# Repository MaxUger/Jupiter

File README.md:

# Jupiter
A 75% hotswappable keyboard PCB with adressable RGB backlighting

__THIS PCB IS UNTESTED, IT PROBABLY DOES NOT WORK__

## Features
- 75% Layout
- Hot-swappable
- Adressable RGB backlighting
- USB-C connectivity
- QMK compatible

## Microcontroller

- Atmel ATmega32u4-MU due to its compatibility with QMK.
- 16MHz crystal oscillator

## USB-C Assembly

- Uses TYPE-C-31-M-14 connector
- PRTR5V0U2X for ESD protection
- 500mA fuse for overcurrent protection

## Switch Matrix

- Features a traditional matrix

## LED Matrices

- Features SK6812MINI-E LEDs

__REMINDER: THIS PCB IS UNTESTED, IT PROBABLY DOES NOT WORK. THIS PROJECT IS PURELY A TECHNICAL EXERCISE__

__This project falls under the GNU General Public License v3.0. This project is provided without liability, warranty, and garentee of functionality.__

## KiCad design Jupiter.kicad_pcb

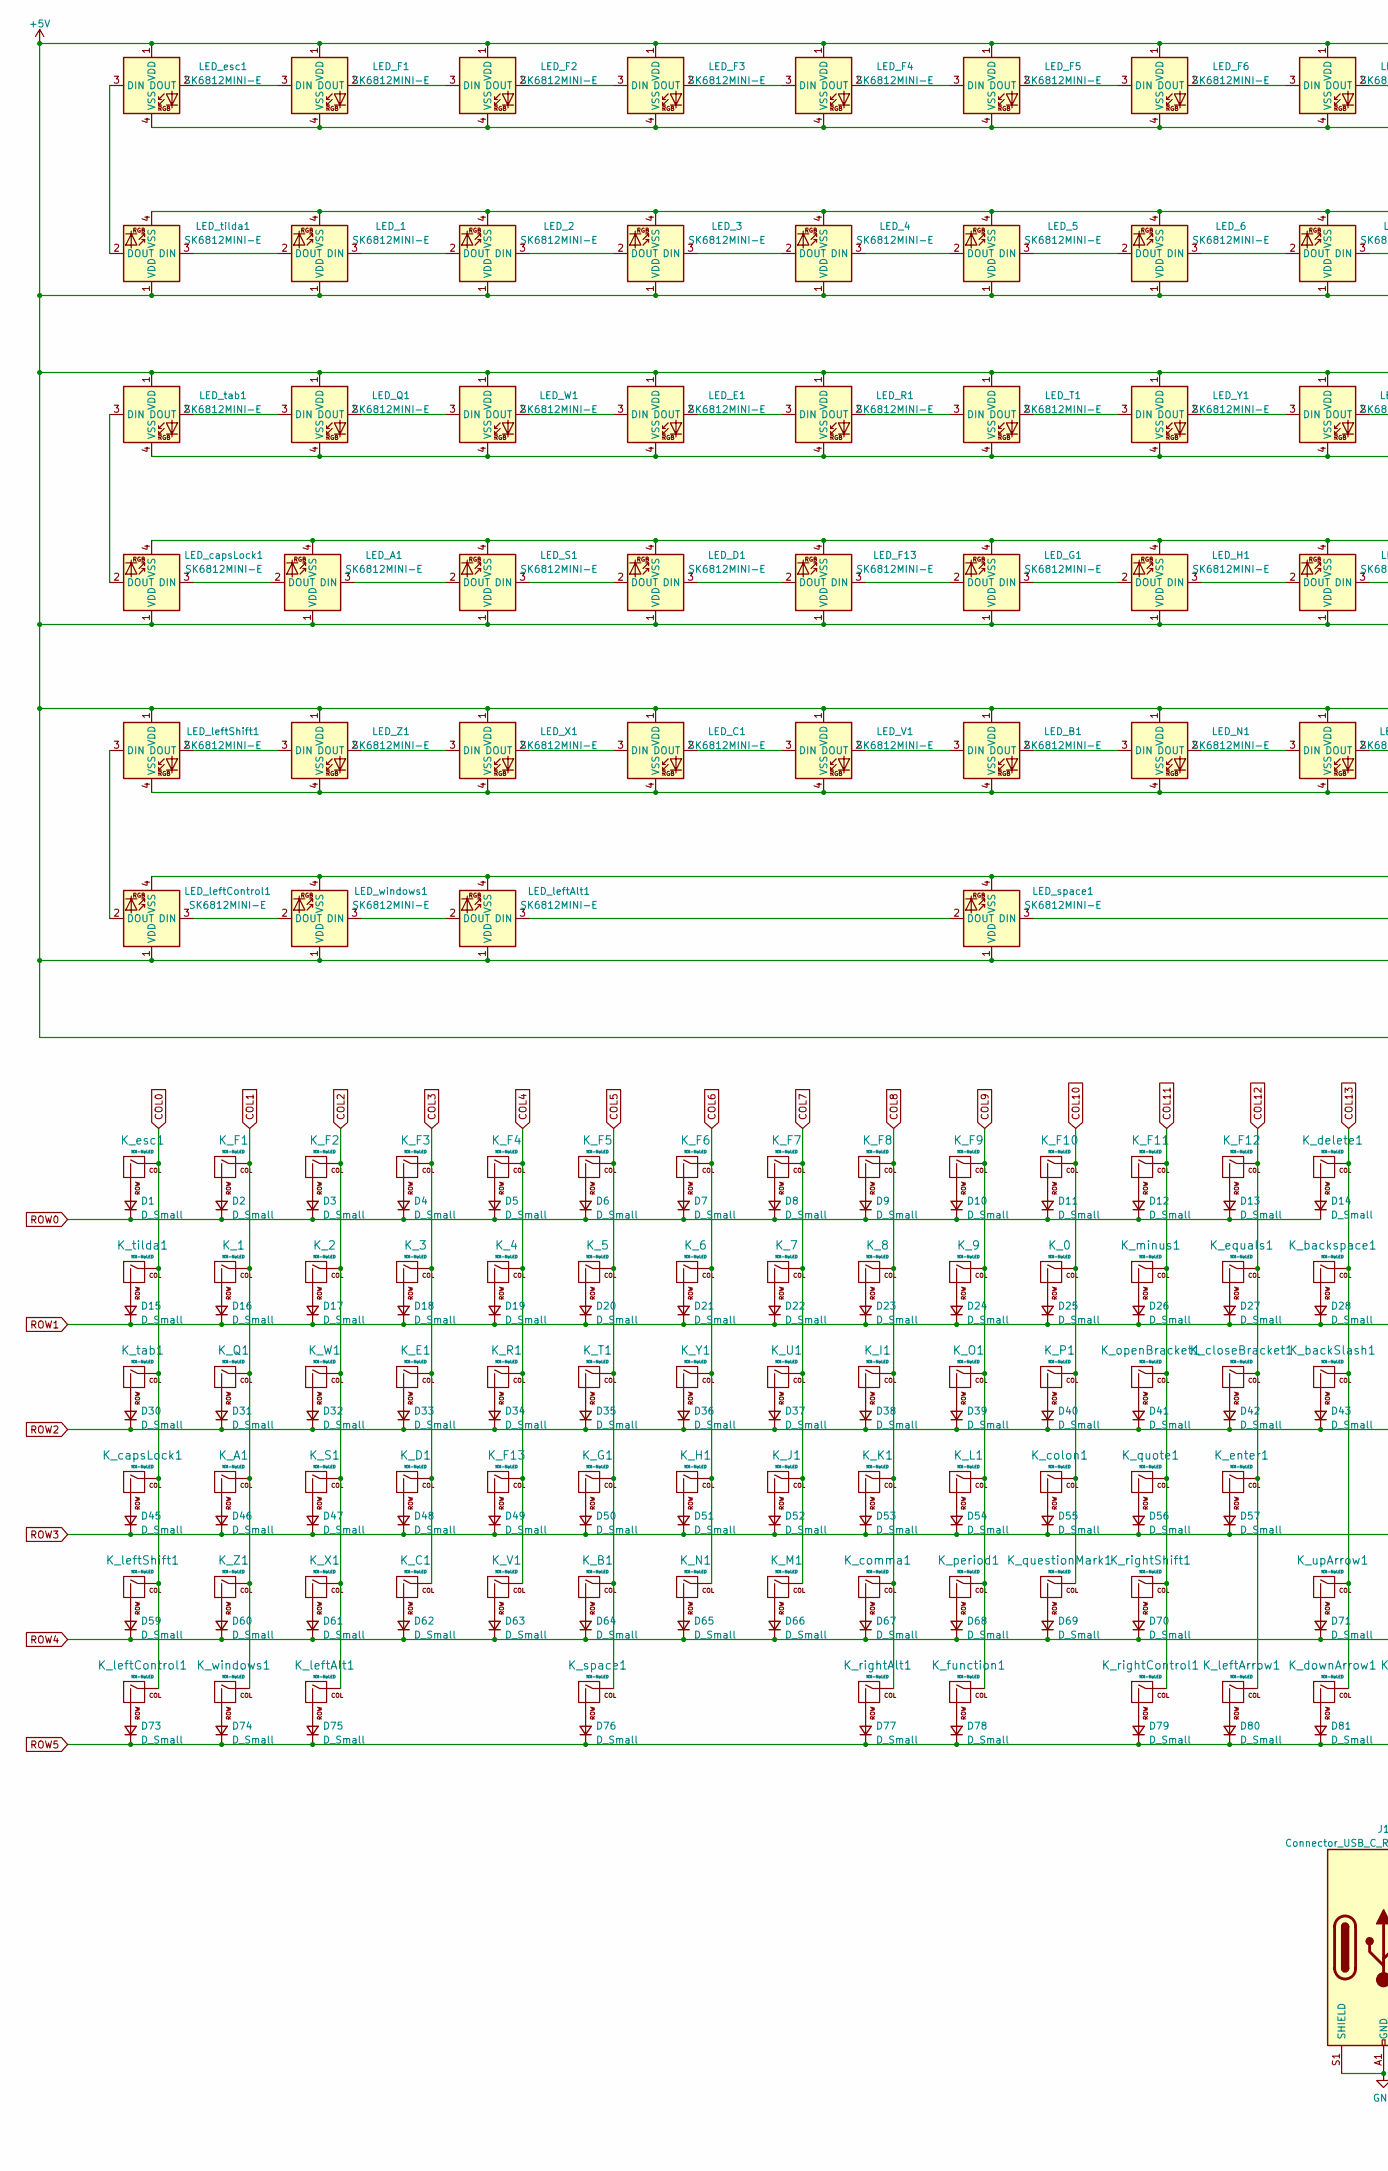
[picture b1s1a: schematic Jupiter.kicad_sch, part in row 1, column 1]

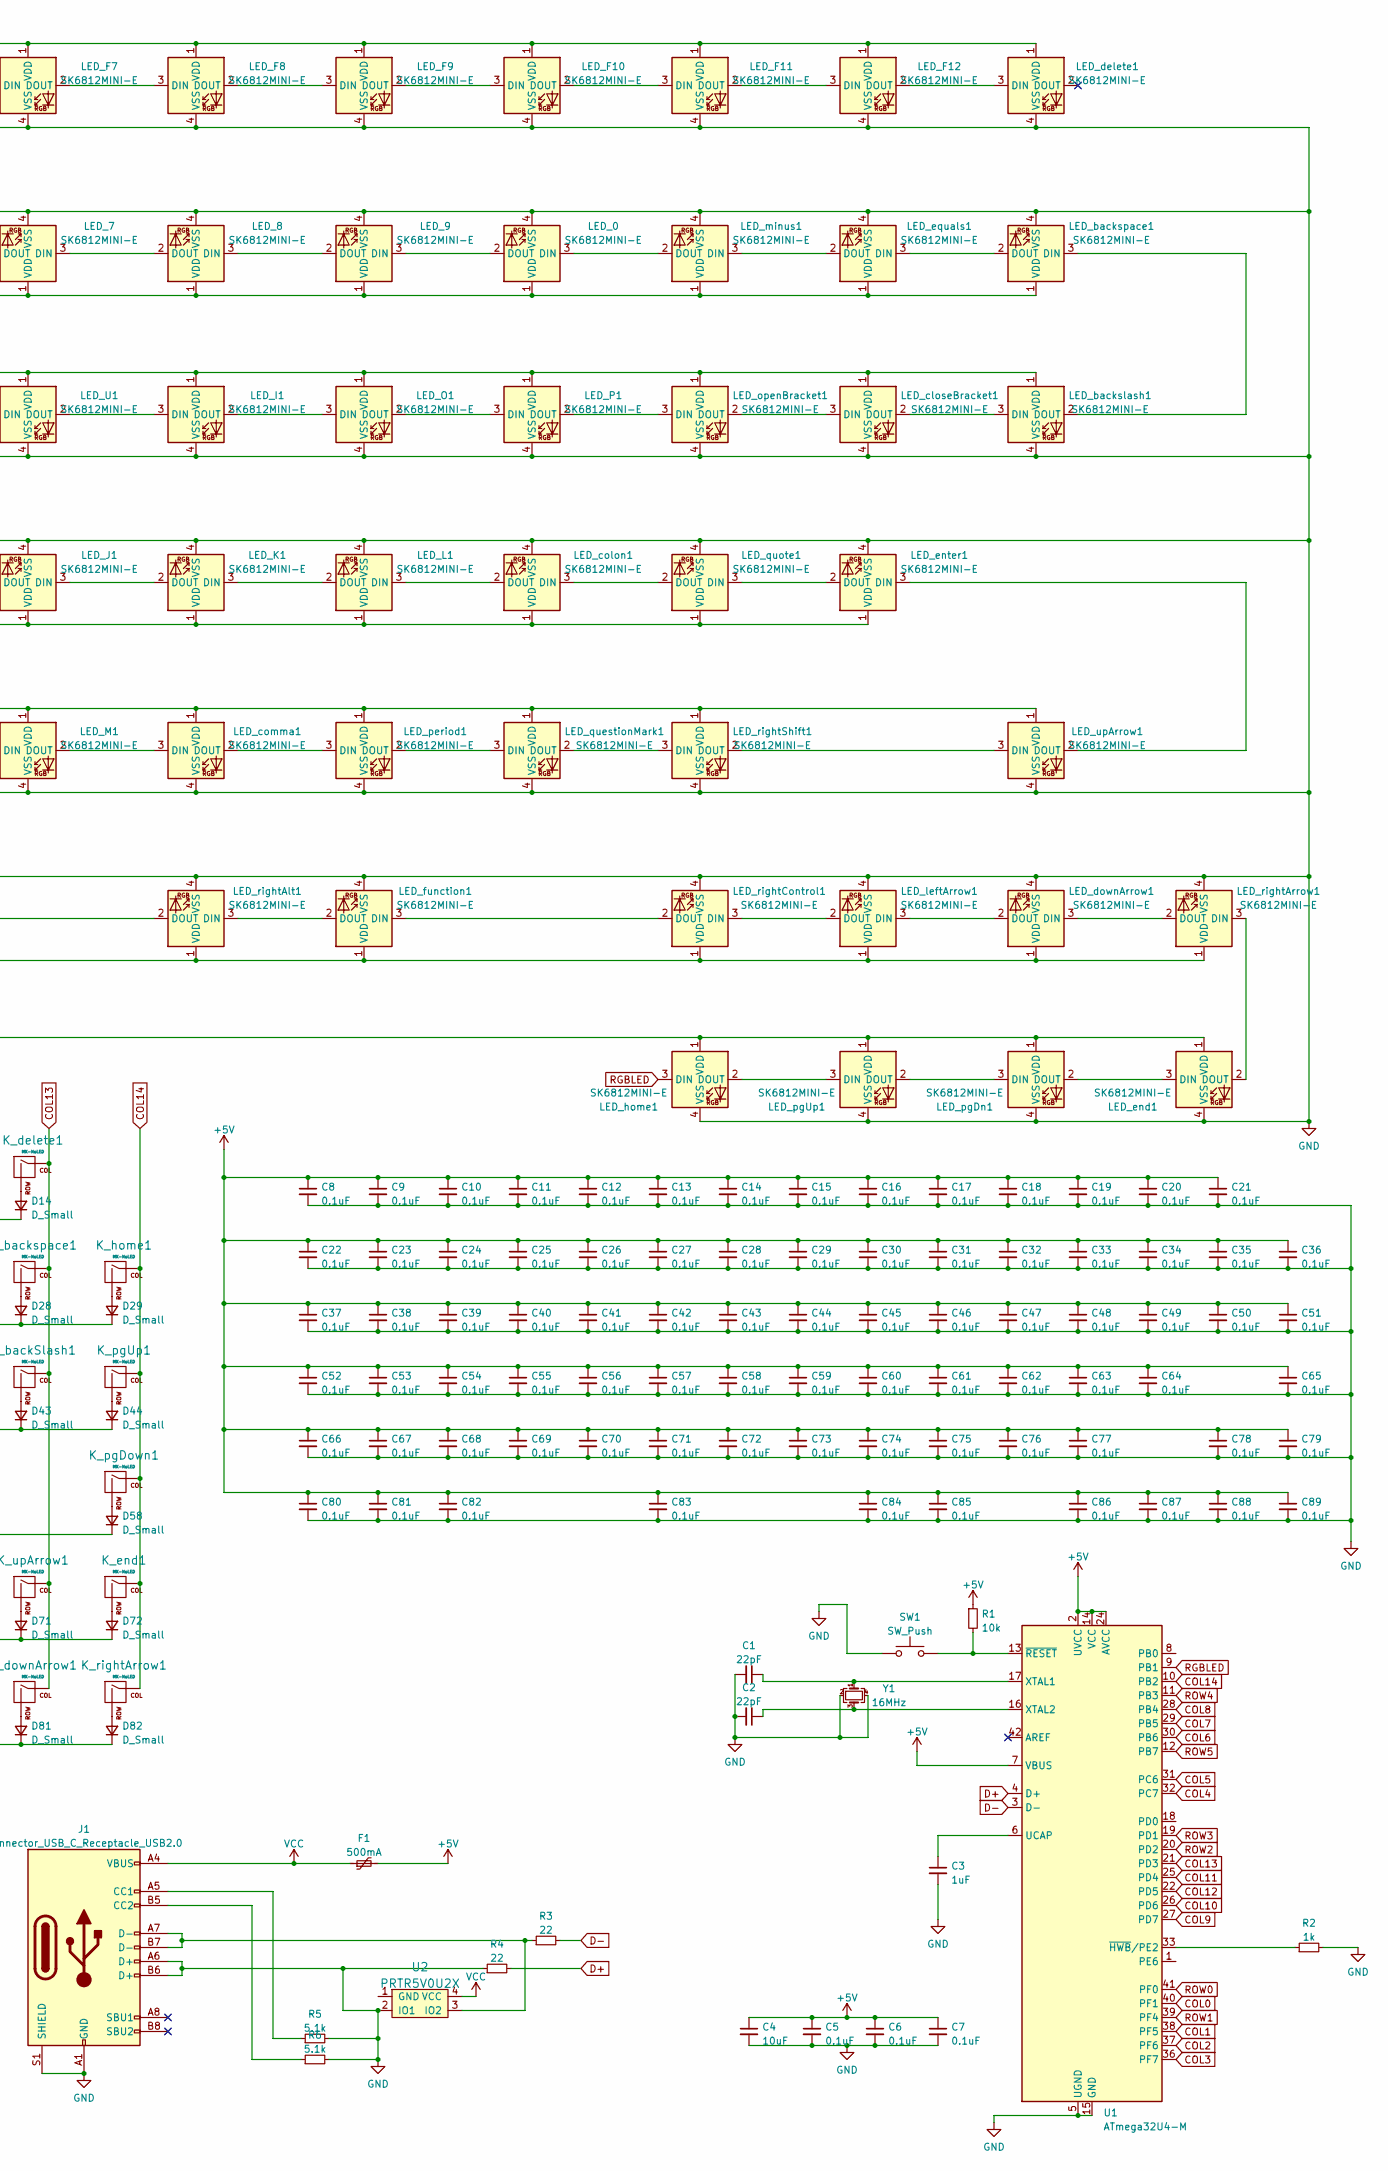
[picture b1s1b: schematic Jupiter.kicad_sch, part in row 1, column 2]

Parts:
C1, C2: 22pF; C_0603_1608Metric
C3: 1uF; C_0603_1608Metric
C4: 10uF; C_0603_1608Metric
C5, C6, C7, C8, C9, C10, C11, C12, C13, C14, C15, C16, C17, C18, C19, C20, C21, C22, C23, C24, C25, C26, C27, C28, C29, C30, C31, C32, C33, C34, C35, C36, C37, C38, C39, C40, C41, C42, C43, C44, C45, C46, C47, C48, C49, C50, C51, C52, C53, C54, C55, C56, C57, C58, C59, C60, C61, C62, C63, C64, C65, C66, C67, C68, C69, C70, C71, C72, C73, C74, C75, C76, C77, C78, C79, C80, C81, C82, C83, C84, C85, C86, C87, C88, C89: 0.1uF; C_0603_1608Metric
D1, D2, D3, D4, D5, D6, D7, D8, D9, D10, D11, D12, D13, D14, D15, D16, D17, D18, D19, D20, D21, D22, D23, D24, D25, D26, D27, D28, D29, D30, D31, D32, D33, D34, D35, D36, D37, D38, D39, D40, D41, D42, D43, D44, D45, D46, D47, D48, D49, D50, D51, D52, D53, D54, D55, D56, D57, D58, D59, D60, D61, D62, D63, D64, D65, D66, D67, D68, D69, D70, D71, D72, D73, D74, D75, D76, D77, D78, D79, D80, D81, D82: D_Small; D_SOD-123
F1: 500mA; Fuse_1206_3216Metric
J1: Connector_USB_C_Receptacle_USB2.0; USB_C_Receptacle_HRO_TYPE-C-31-M-14
K_0, K_1, K_2, K_3, K_4, K_5, K_6, K_7, K_8, K_9: MX-NoLED; SW_MX_HS_1u
K_A1: MX-NoLED; SW_MX_HS_1u
K_B1: MX-NoLED; SW_MX_HS_1u
K_C1: MX-NoLED; SW_MX_HS_1u
K_D1: MX-NoLED; SW_MX_HS_1u
K_E1: MX-NoLED; SW_MX_HS_1u
K_F1, K_F2, K_F3, K_F4, K_F5, K_F6, K_F7, K_F8, K_F9, K_F10, K_F11, K_F12, K_F13: MX-NoLED; SW_MX_HS_1u
K_G1: MX-NoLED; SW_MX_HS_1u
K_H1: MX-NoLED; SW_MX_HS_1u
K_I1: MX-NoLED; SW_MX_HS_1u
K_J1: MX-NoLED; SW_MX_HS_1u
K_K1: MX-NoLED; SW_MX_HS_1u
K_L1: MX-NoLED; SW_MX_HS_1u
K_M1: MX-NoLED; SW_MX_HS_1u
K_N1: MX-NoLED; SW_MX_HS_1u
K_O1: MX-NoLED; SW_MX_HS_1u
K_P1: MX-NoLED; SW_MX_HS_1u
K_Q1: MX-NoLED; SW_MX_HS_1u
K_R1: MX-NoLED; SW_MX_HS_1u
K_S1: MX-NoLED; SW_MX_HS_1u
K_T1: MX-NoLED; SW_MX_HS_1u
K_U1: MX-NoLED; SW_MX_HS_1u
K_V1: MX-NoLED; SW_MX_HS_1u
K_W1: MX-NoLED; SW_MX_HS_1u
K_X1: MX-NoLED; SW_MX_HS_1u
K_Y1: MX-NoLED; SW_MX_HS_1u
K_Z1: MX-NoLED; SW_MX_HS_1u
K_backSlash1: MX-NoLED; SW_MX_HS_1u
K_backspace1: MX-NoLED; SW_MX_HS_1u
K_capsLock1: MX-NoLED; SW_MX_HS_1u
K_closeBracket1: MX-NoLED; SW_MX_HS_1u
K_colon1: MX-NoLED; SW_MX_HS_1u
K_comma1: MX-NoLED; SW_MX_HS_1u
K_delete1: MX-NoLED; SW_MX_HS_1u
K_downArrow1: MX-NoLED; SW_MX_HS_1u
K_end1: MX-NoLED; SW_MX_HS_1u
K_enter1: MX-NoLED; SW_MX_HS_1u
K_equals1: MX-NoLED; SW_MX_HS_1u
K_esc1: MX-NoLED; SW_MX_HS_1u
K_function1: MX-NoLED; SW_MX_HS_1u
K_home1: MX-NoLED; SW_MX_HS_1u
K_leftAlt1: MX-NoLED; SW_MX_HS_1u
K_leftArrow1: MX-NoLED; SW_MX_HS_1u
K_leftControl1: MX-NoLED; SW_MX_HS_1u
K_leftShift1: MX-NoLED; SW_MX_HS_1u
K_minus1: MX-NoLED; SW_MX_HS_1u
K_openBracket1: MX-NoLED; SW_MX_HS_1u
K_period1: MX-NoLED; SW_MX_HS_1u
K_pgDown1: MX-NoLED; SW_MX_HS_1u
K_pgUp1: MX-NoLED; SW_MX_HS_1u
K_questionMark1: MX-NoLED; SW_MX_HS_1u
K_quote1: MX-NoLED; SW_MX_HS_1u
K_rightAlt1: MX-NoLED; SW_MX_HS_1u
K_rightArrow1: MX-NoLED; SW_MX_HS_1u
K_rightControl1: MX-NoLED; SW_MX_HS_1u
K_rightShift1: MX-NoLED; SW_MX_HS_1u
K_space1: MX-NoLED; SW_MX_HS_1u
K_tab1: MX-NoLED; SW_MX_HS_1u
K_tilda1: MX-NoLED; SW_MX_HS_1u
K_upArrow1: MX-NoLED; SW_MX_HS_1u
K_windows1: MX-NoLED; SW_MX_HS_1u
LED_0, LED_1, LED_2, LED_3, LED_4, LED_5, LED_6, LED_7, LED_8, LED_9: SK6812MINI-E; LED_MX_6028R
LED_A1: SK6812MINI-E; LED_MX_6028R
LED_B1: SK6812MINI-E; LED_MX_6028R-FLIPPED
LED_C1: SK6812MINI-E; LED_MX_6028R-FLIPPED
LED_D1: SK6812MINI-E; LED_MX_6028R
LED_E1: SK6812MINI-E; LED_MX_6028R-FLIPPED
LED_F1, LED_F2, LED_F3, LED_F4, LED_F5, LED_F6, LED_F7, LED_F8, LED_F9, LED_F10, LED_F11, LED_F12: SK6812MINI-E; LED_MX_6028R-FLIPPED
LED_F13: SK6812MINI-E; LED_MX_6028R
LED_G1: SK6812MINI-E; LED_MX_6028R
LED_H1: SK6812MINI-E; LED_MX_6028R
LED_I1: SK6812MINI-E; LED_MX_6028R-FLIPPED
LED_J1: SK6812MINI-E; LED_MX_6028R
LED_K1: SK6812MINI-E; LED_MX_6028R
LED_L1: SK6812MINI-E; LED_MX_6028R
LED_M1: SK6812MINI-E; LED_MX_6028R-FLIPPED
LED_N1: SK6812MINI-E; LED_MX_6028R-FLIPPED
LED_O1: SK6812MINI-E; LED_MX_6028R-FLIPPED
LED_P1: SK6812MINI-E; LED_MX_6028R-FLIPPED
LED_Q1: SK6812MINI-E; LED_MX_6028R-FLIPPED
LED_R1: SK6812MINI-E; LED_MX_6028R-FLIPPED
LED_S1: SK6812MINI-E; LED_MX_6028R
LED_T1: SK6812MINI-E; LED_MX_6028R-FLIPPED
LED_U1: SK6812MINI-E; LED_MX_6028R-FLIPPED
LED_V1: SK6812MINI-E; LED_MX_6028R-FLIPPED
LED_W1: SK6812MINI-E; LED_MX_6028R-FLIPPED
LED_X1: SK6812MINI-E; LED_MX_6028R-FLIPPED
LED_Y1: SK6812MINI-E; LED_MX_6028R-FLIPPED
LED_Z1: SK6812MINI-E; LED_MX_6028R-FLIPPED
LED_backslash1: SK6812MINI-E; LED_MX_6028R-FLIPPED
LED_backspace1: SK6812MINI-E; LED_MX_6028R
LED_capsLock1: SK6812MINI-E; LED_MX_6028R
LED_closeBracket1: SK6812MINI-E; LED_MX_6028R-FLIPPED
LED_colon1: SK6812MINI-E; LED_MX_6028R
LED_comma1: SK6812MINI-E; LED_MX_6028R-FLIPPED
LED_delete1: SK6812MINI-E; LED_MX_6028R-FLIPPED
LED_downArrow1: SK6812MINI-E; LED_MX_6028R
LED_end1: SK6812MINI-E; LED_MX_6028R
LED_enter1: SK6812MINI-E; LED_MX_6028R
LED_equals1: SK6812MINI-E; LED_MX_6028R
LED_esc1: SK6812MINI-E; LED_MX_6028R-FLIPPED
LED_function1: SK6812MINI-E; LED_MX_6028R
LED_home1: SK6812MINI-E; LED_MX_6028R-FLIPPED
LED_leftAlt1: SK6812MINI-E; LED_MX_6028R
LED_leftArrow1: SK6812MINI-E; LED_MX_6028R
LED_leftControl1: SK6812MINI-E; LED_MX_6028R
LED_leftShift1: SK6812MINI-E; LED_MX_6028R-FLIPPED
LED_minus1: SK6812MINI-E; LED_MX_6028R
LED_openBracket1: SK6812MINI-E; LED_MX_6028R-FLIPPED
LED_period1: SK6812MINI-E; LED_MX_6028R-FLIPPED
LED_pgDn1: SK6812MINI-E; LED_MX_6028R
LED_pgUp1: SK6812MINI-E; LED_MX_6028R
LED_questionMark1: SK6812MINI-E; LED_MX_6028R-FLIPPED
LED_quote1: SK6812MINI-E; LED_MX_6028R
LED_rightAlt1: SK6812MINI-E; LED_MX_6028R
LED_rightArrow1: SK6812MINI-E; LED_MX_6028R
LED_rightControl1: SK6812MINI-E; LED_MX_6028R
LED_rightShift1: SK6812MINI-E; LED_MX_6028R-FLIPPED
LED_space1: SK6812MINI-E; LED_MX_6028R
LED_tab1: SK6812MINI-E; LED_MX_6028R-FLIPPED
LED_tilda1: SK6812MINI-E; LED_MX_6028R
LED_upArrow1: SK6812MINI-E; LED_MX_6028R-FLIPPED
LED_windows1: SK6812MINI-E; LED_MX_6028R
R1: 10k; R_0603_1608Metric
R2: 1k; R_0603_1608Metric
R3, R4: 22; R_0603_1608Metric
R5, R6: 5.1k; R_0603_1608Metric
SW1: SW_Push; SKQG-1155865
U1: ATmega32U4-M; QFN-44-1EP_7x7mm_P0.5mm_EP5.2x5.2mm
U2: PRTR5V0U2X; SOT143B
Y1: 16MHz; Crystal_SMD_3225-4Pin_3.2x2.5mm

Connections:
+5V: C4.1, C5.1, C6.1, C7.1, C8.1, C9.1, C10.1, C11.1, C12.1, C13.1, C14.1, C15.1, C16.1, C17.1, C18.1, C19.1, C20.1, C21.1, C22.1, C23.1, C24.1, C25.1, C26.1, C27.1, C28.1, C29.1, C30.1, C31.1, C32.1, C33.1, C34.1, C35.1, C36.1, C37.1, C38.1, C39.1, C40.1, C41.1, C42.1, C43.1, C44.1, C45.1, C46.1, C47.1, C48.1, C49.1, C50.1, C51.1, C52.1, C53.1, C54.1, C55.1, C56.1, C57.1, C58.1, C59.1, C60.1, C61.1, C62.1, C63.1, C64.1, C65.1, C66.1, C67.1, C68.1, C69.1, C70.1, C71.1, C72.1, C73.1, C74.1, C75.1, C76.1, C77.1, C78.1, C79.1, C80.1, C81.1, C82.1, C83.1, C84.1, C85.1, C86.1, C87.1, C88.1, C89.1, F1.2, LED_0.1 (VDD), LED_1.1 (VDD), LED_2.1 (VDD), LED_3.1 (VDD), LED_4.1 (VDD), LED_5.1 (VDD), LED_6.1 (VDD), LED_7.1 (VDD), LED_8.1 (VDD), LED_9.1 (VDD), LED_A1.1 (VDD), LED_B1.1 (VDD), LED_C1.1 (VDD), LED_D1.1 (VDD), LED_E1.1 (VDD), LED_F1.1 (VDD), LED_F2.1 (VDD), LED_F3.1 (VDD), LED_F4.1 (VDD), LED_F5.1 (VDD), LED_F6.1 (VDD), LED_F7.1 (VDD), LED_F8.1 (VDD), LED_F9.1 (VDD), LED_F10.1 (VDD), LED_F11.1 (VDD), LED_F12.1 (VDD), LED_F13.1 (VDD), LED_G1.1 (VDD), LED_H1.1 (VDD), LED_I1.1 (VDD), LED_J1.1 (VDD), LED_K1.1 (VDD), LED_L1.1 (VDD), LED_M1.1 (VDD), LED_N1.1 (VDD), LED_O1.1 (VDD), LED_P1.1 (VDD), LED_Q1.1 (VDD), LED_R1.1 (VDD), LED_S1.1 (VDD), LED_T1.1 (VDD), LED_U1.1 (VDD), LED_V1.1 (VDD), LED_W1.1 (VDD), LED_X1.1 (VDD), LED_Y1.1 (VDD), LED_Z1.1 (VDD), LED_backslash1.1 (VDD), LED_backspace1.1 (VDD), LED_capsLock1.1 (VDD), LED_closeBracket1.1 (VDD), LED_colon1.1 (VDD), LED_comma1.1 (VDD), LED_delete1.1 (VDD), LED_downArrow1.1 (VDD), LED_end1.1 (VDD), LED_enter1.1 (VDD), LED_equals1.1 (VDD), LED_esc1.1 (VDD), LED_function1.1 (VDD), LED_home1.1 (VDD), LED_leftAlt1.1 (VDD), LED_leftArrow1.1 (VDD), LED_leftControl1.1 (VDD), LED_leftShift1.1 (VDD), LED_minus1.1 (VDD), LED_openBracket1.1 (VDD), LED_period1.1 (VDD), LED_pgDn1.1 (VDD), LED_pgUp1.1 (VDD), LED_questionMark1.1 (VDD), LED_quote1.1 (VDD), LED_rightAlt1.1 (VDD), LED_rightArrow1.1 (VDD), LED_rightControl1.1 (VDD), LED_rightShift1.1 (VDD), LED_space1.1 (VDD), LED_tab1.1 (VDD), LED_tilda1.1 (VDD), LED_upArrow1.1 (VDD), LED_windows1.1 (VDD), R1.1, U1.2 (UVCC), U1.7 (VBUS), U1.14 (VCC), U1.24 (AVCC), U1.34 (VCC), U1.44 (AVCC)
COL0: K_capsLock1.1 (COL), K_esc1.1 (COL), K_leftControl1.1 (COL), K_leftShift1.1 (COL), K_tab1.1 (COL), K_tilda1.1 (COL), U1.40 (PF1)
COL1: K_1.1 (COL), K_A1.1 (COL), K_F1.1 (COL), K_Q1.1 (COL), K_Z1.1 (COL), K_windows1.1 (COL), U1.38 (PF5)
COL2: K_2.1 (COL), K_F2.1 (COL), K_S1.1 (COL), K_W1.1 (COL), K_X1.1 (COL), K_leftAlt1.1 (COL), U1.37 (PF6)
COL3: K_3.1 (COL), K_C1.1 (COL), K_D1.1 (COL), K_E1.1 (COL), K_F3.1 (COL), U1.36 (PF7)
COL4: K_4.1 (COL), K_F4.1 (COL), K_F13.1 (COL), K_R1.1 (COL), K_V1.1 (COL), U1.32 (PC7)
COL5: K_5.1 (COL), K_B1.1 (COL), K_F5.1 (COL), K_G1.1 (COL), K_T1.1 (COL), K_space1.1 (COL), U1.31 (PC6)
COL6: K_6.1 (COL), K_F6.1 (COL), K_H1.1 (COL), K_N1.1 (COL), K_Y1.1 (COL), U1.30 (PB6)
COL7: K_7.1 (COL), K_F7.1 (COL), K_J1.1 (COL), K_M1.1 (COL), K_U1.1 (COL), U1.29 (PB5)
COL8: K_8.1 (COL), K_F8.1 (COL), K_I1.1 (COL), K_K1.1 (COL), K_comma1.1 (COL), K_rightAlt1.1 (COL), U1.28 (PB4)
COL9: K_9.1 (COL), K_F9.1 (COL), K_L1.1 (COL), K_O1.1 (COL), K_function1.1 (COL), K_period1.1 (COL), U1.27 (PD7)
COL10: K_0.1 (COL), K_F10.1 (COL), K_P1.1 (COL), K_colon1.1 (COL), K_questionMark1.1 (COL), U1.26 (PD6)
COL11: K_F11.1 (COL), K_minus1.1 (COL), K_openBracket1.1 (COL), K_quote1.1 (COL), K_rightControl1.1 (COL), K_rightShift1.1 (COL), U1.25 (PD4)
COL12: K_F12.1 (COL), K_closeBracket1.1 (COL), K_enter1.1 (COL), K_equals1.1 (COL), K_leftArrow1.1 (COL), U1.22 (PD5)
COL13: K_backSlash1.1 (COL), K_backspace1.1 (COL), K_delete1.1 (COL), K_downArrow1.1 (COL), K_upArrow1.1 (COL), U1.21 (PD3)
COL14: K_end1.1 (COL), K_home1.1 (COL), K_pgDown1.1 (COL), K_pgUp1.1 (COL), K_rightArrow1.1 (COL), U1.10 (PB2)
D+: R4.2, U1.4 (D+)
D-: R3.2, U1.3 (D-)
unnamed: C1.1, U1.17 (XTAL1), Y1.1
unnamed: C2.1, U1.16 (XTAL2), Y1.3
unnamed: C3.1, U1.6 (UCAP)
unnamed: D1.2 (A), K_esc1.2 (ROW)
unnamed: D2.2 (A), K_F1.2 (ROW)
unnamed: D3.2 (A), K_F2.2 (ROW)
unnamed: D4.2 (A), K_F3.2 (ROW)
unnamed: D5.2 (A), K_F4.2 (ROW)
unnamed: D6.2 (A), K_F5.2 (ROW)
unnamed: D7.2 (A), K_F6.2 (ROW)
unnamed: D8.2 (A), K_F7.2 (ROW)
unnamed: D9.2 (A), K_F8.2 (ROW)
unnamed: D10.2 (A), K_F9.2 (ROW)
unnamed: D11.2 (A), K_F10.2 (ROW)
unnamed: D12.2 (A), K_F11.2 (ROW)
unnamed: D13.2 (A), K_F12.2 (ROW)
unnamed: D14.2 (A), K_delete1.2 (ROW)
unnamed: D15.2 (A), K_tilda1.2 (ROW)
unnamed: D16.2 (A), K_1.2 (ROW)
unnamed: D17.2 (A), K_2.2 (ROW)
unnamed: D18.2 (A), K_3.2 (ROW)
unnamed: D19.2 (A), K_4.2 (ROW)
unnamed: D20.2 (A), K_5.2 (ROW)
unnamed: D21.2 (A), K_6.2 (ROW)
unnamed: D22.2 (A), K_7.2 (ROW)
unnamed: D23.2 (A), K_8.2 (ROW)
unnamed: D24.2 (A), K_9.2 (ROW)
unnamed: D25.2 (A), K_0.2 (ROW)
unnamed: D26.2 (A), K_minus1.2 (ROW)
unnamed: D27.2 (A), K_equals1.2 (ROW)
unnamed: D28.2 (A), K_backspace1.2 (ROW)
unnamed: D29.2 (A), K_home1.2 (ROW)
unnamed: D30.2 (A), K_tab1.2 (ROW)
unnamed: D31.2 (A), K_Q1.2 (ROW)
unnamed: D32.2 (A), K_W1.2 (ROW)
unnamed: D33.2 (A), K_E1.2 (ROW)
unnamed: D34.2 (A), K_R1.2 (ROW)
unnamed: D35.2 (A), K_T1.2 (ROW)
unnamed: D36.2 (A), K_Y1.2 (ROW)
unnamed: D37.2 (A), K_U1.2 (ROW)
unnamed: D38.2 (A), K_I1.2 (ROW)
unnamed: D39.2 (A), K_O1.2 (ROW)
unnamed: D40.2 (A), K_P1.2 (ROW)
unnamed: D41.2 (A), K_openBracket1.2 (ROW)
unnamed: D42.2 (A), K_closeBracket1.2 (ROW)
unnamed: D43.2 (A), K_backSlash1.2 (ROW)
unnamed: D44.2 (A), K_pgUp1.2 (ROW)
unnamed: D45.2 (A), K_capsLock1.2 (ROW)
unnamed: D46.2 (A), K_A1.2 (ROW)
unnamed: D47.2 (A), K_S1.2 (ROW)
unnamed: D48.2 (A), K_D1.2 (ROW)
unnamed: D49.2 (A), K_F13.2 (ROW)
unnamed: D50.2 (A), K_G1.2 (ROW)
unnamed: D51.2 (A), K_H1.2 (ROW)
unnamed: D52.2 (A), K_J1.2 (ROW)
unnamed: D53.2 (A), K_K1.2 (ROW)
unnamed: D54.2 (A), K_L1.2 (ROW)
unnamed: D55.2 (A), K_colon1.2 (ROW)
unnamed: D56.2 (A), K_quote1.2 (ROW)
unnamed: D57.2 (A), K_enter1.2 (ROW)
unnamed: D58.2 (A), K_pgDown1.2 (ROW)
unnamed: D59.2 (A), K_leftShift1.2 (ROW)
unnamed: D60.2 (A), K_Z1.2 (ROW)
unnamed: D61.2 (A), K_X1.2 (ROW)
unnamed: D62.2 (A), K_C1.2 (ROW)
unnamed: D63.2 (A), K_V1.2 (ROW)
unnamed: D64.2 (A), K_B1.2 (ROW)
unnamed: D65.2 (A), K_N1.2 (ROW)
unnamed: D66.2 (A), K_M1.2 (ROW)
unnamed: D67.2 (A), K_comma1.2 (ROW)
unnamed: D68.2 (A), K_period1.2 (ROW)
unnamed: D69.2 (A), K_questionMark1.2 (ROW)
unnamed: D70.2 (A), K_rightShift1.2 (ROW)
unnamed: D71.2 (A), K_upArrow1.2 (ROW)
unnamed: D72.2 (A), K_end1.2 (ROW)
unnamed: D73.2 (A), K_leftControl1.2 (ROW)
unnamed: D74.2 (A), K_windows1.2 (ROW)
unnamed: D75.2 (A), K_leftAlt1.2 (ROW)
unnamed: D76.2 (A), K_space1.2 (ROW)
unnamed: D77.2 (A), K_rightAlt1.2 (ROW)
unnamed: D78.2 (A), K_function1.2 (ROW)
unnamed: D79.2 (A), K_rightControl1.2 (ROW)
unnamed: D80.2 (A), K_leftArrow1.2 (ROW)
unnamed: D81.2 (A), K_downArrow1.2 (ROW)
unnamed: D82.2 (A), K_rightArrow1.2 (ROW)
unnamed: J1.A5 (CC1), R5.1
unnamed: J1.A7 (D-), J1.B7 (D-), R3.1, U2.3 (IO2)
unnamed: J1.B5 (CC2), R6.1
unnamed: LED_0.2 (DOUT), LED_9.3 (DIN)
unnamed: LED_0.3 (DIN), LED_minus1.2 (DOUT)
unnamed: LED_1.2 (DOUT), LED_tilda1.3 (DIN)
unnamed: LED_1.3 (DIN), LED_2.2 (DOUT)
unnamed: LED_2.3 (DIN), LED_3.2 (DOUT)
unnamed: LED_3.3 (DIN), LED_4.2 (DOUT)
unnamed: LED_4.3 (DIN), LED_5.2 (DOUT)
unnamed: LED_5.3 (DIN), LED_6.2 (DOUT)
unnamed: LED_6.3 (DIN), LED_7.2 (DOUT)
unnamed: LED_7.3 (DIN), LED_8.2 (DOUT)
unnamed: LED_8.3 (DIN), LED_9.2 (DOUT)
unnamed: LED_A1.2 (DOUT), LED_capsLock1.3 (DIN)
unnamed: LED_A1.3 (DIN), LED_S1.2 (DOUT)
unnamed: LED_B1.2 (DOUT), LED_N1.3 (DIN)
unnamed: LED_B1.3 (DIN), LED_V1.2 (DOUT)
unnamed: LED_C1.2 (DOUT), LED_V1.3 (DIN)
unnamed: LED_C1.3 (DIN), LED_X1.2 (DOUT)
unnamed: LED_D1.2 (DOUT), LED_S1.3 (DIN)
unnamed: LED_D1.3 (DIN), LED_F13.2 (DOUT)
unnamed: LED_E1.2 (DOUT), LED_R1.3 (DIN)
unnamed: LED_E1.3 (DIN), LED_W1.2 (DOUT)
unnamed: LED_F1.2 (DOUT), LED_F2.3 (DIN)
unnamed: LED_F1.3 (DIN), LED_esc1.2 (DOUT)
unnamed: LED_F2.2 (DOUT), LED_F3.3 (DIN)
unnamed: LED_F3.2 (DOUT), LED_F4.3 (DIN)
unnamed: LED_F4.2 (DOUT), LED_F5.3 (DIN)
unnamed: LED_F5.2 (DOUT), LED_F6.3 (DIN)
unnamed: LED_F6.2 (DOUT), LED_F7.3 (DIN)
unnamed: LED_F7.2 (DOUT), LED_F8.3 (DIN)
unnamed: LED_F8.2 (DOUT), LED_F9.3 (DIN)
unnamed: LED_F10.2 (DOUT), LED_F11.3 (DIN)
unnamed: LED_F9.2 (DOUT), LED_F10.3 (DIN)
unnamed: LED_F11.2 (DOUT), LED_F12.3 (DIN)
unnamed: LED_F12.2 (DOUT), LED_delete1.3 (DIN)
unnamed: LED_F13.3 (DIN), LED_G1.2 (DOUT)
unnamed: LED_G1.3 (DIN), LED_H1.2 (DOUT)
unnamed: LED_H1.3 (DIN), LED_J1.2 (DOUT)
unnamed: LED_I1.2 (DOUT), LED_O1.3 (DIN)
unnamed: LED_I1.3 (DIN), LED_U1.2 (DOUT)
unnamed: LED_J1.3 (DIN), LED_K1.2 (DOUT)
unnamed: LED_K1.3 (DIN), LED_L1.2 (DOUT)
unnamed: LED_L1.3 (DIN), LED_colon1.2 (DOUT)
unnamed: LED_M1.2 (DOUT), LED_comma1.3 (DIN)
unnamed: LED_M1.3 (DIN), LED_N1.2 (DOUT)
unnamed: LED_O1.2 (DOUT), LED_P1.3 (DIN)
unnamed: LED_P1.2 (DOUT), LED_openBracket1.3 (DIN)
unnamed: LED_Q1.2 (DOUT), LED_W1.3 (DIN)
unnamed: LED_Q1.3 (DIN), LED_tab1.2 (DOUT)
unnamed: LED_R1.2 (DOUT), LED_T1.3 (DIN)
unnamed: LED_T1.2 (DOUT), LED_Y1.3 (DIN)
unnamed: LED_U1.3 (DIN), LED_Y1.2 (DOUT)
unnamed: LED_X1.3 (DIN), LED_Z1.2 (DOUT)
unnamed: LED_Z1.3 (DIN), LED_leftShift1.2 (DOUT)
unnamed: LED_backslash1.2 (DOUT), LED_backspace1.3 (DIN)
unnamed: LED_backslash1.3 (DIN), LED_closeBracket1.2 (DOUT)
unnamed: LED_backspace1.2 (DOUT), LED_equals1.3 (DIN)
unnamed: LED_capsLock1.2 (DOUT), LED_tab1.3 (DIN)
unnamed: LED_closeBracket1.3 (DIN), LED_openBracket1.2 (DOUT)
unnamed: LED_colon1.3 (DIN), LED_quote1.2 (DOUT)
unnamed: LED_comma1.2 (DOUT), LED_period1.3 (DIN)
unnamed: LED_downArrow1.2 (DOUT), LED_leftArrow1.3 (DIN)
unnamed: LED_downArrow1.3 (DIN), LED_rightArrow1.2 (DOUT)
unnamed: LED_end1.2 (DOUT), LED_rightArrow1.3 (DIN)
unnamed: LED_end1.3 (DIN), LED_pgDn1.2 (DOUT)
unnamed: LED_enter1.2 (DOUT), LED_quote1.3 (DIN)
unnamed: LED_enter1.3 (DIN), LED_upArrow1.2 (DOUT)
unnamed: LED_equals1.2 (DOUT), LED_minus1.3 (DIN)
unnamed: LED_esc1.3 (DIN), LED_tilda1.2 (DOUT)
unnamed: LED_function1.2 (DOUT), LED_rightAlt1.3 (DIN)
unnamed: LED_function1.3 (DIN), LED_rightControl1.2 (DOUT)
unnamed: LED_home1.2 (DOUT), LED_pgUp1.3 (DIN)
unnamed: LED_leftAlt1.2 (DOUT), LED_windows1.3 (DIN)
unnamed: LED_leftAlt1.3 (DIN), LED_space1.2 (DOUT)
unnamed: LED_leftArrow1.2 (DOUT), LED_rightControl1.3 (DIN)
unnamed: LED_leftControl1.2 (DOUT), LED_leftShift1.3 (DIN)
unnamed: LED_leftControl1.3 (DIN), LED_windows1.2 (DOUT)
unnamed: LED_period1.2 (DOUT), LED_questionMark1.3 (DIN)
unnamed: LED_pgDn1.3 (DIN), LED_pgUp1.2 (DOUT)
unnamed: LED_questionMark1.2 (DOUT), LED_rightShift1.3 (DIN)
unnamed: LED_rightAlt1.2 (DOUT), LED_space1.3 (DIN)
unnamed: LED_rightShift1.2 (DOUT), LED_upArrow1.3 (DIN)
unnamed: R1.2, SW1.2, U1.13 (~RESET)
unnamed: R2.1, U1.33 (~HWB/PE2)
RGBLED: LED_home1.3 (DIN), U1.9 (PB1)
ROW0: D1.1 (K), D2.1 (K), D3.1 (K), D4.1 (K), D5.1 (K), D6.1 (K), D7.1 (K), D8.1 (K), D9.1 (K), D10.1 (K), D11.1 (K), D12.1 (K), D13.1 (K), D14.1 (K), U1.41 (PF0)
ROW1: D15.1 (K), D16.1 (K), D17.1 (K), D18.1 (K), D19.1 (K), D20.1 (K), D21.1 (K), D22.1 (K), D23.1 (K), D24.1 (K), D25.1 (K), D26.1 (K), D27.1 (K), D28.1 (K), D29.1 (K), U1.39 (PF4)
ROW2: D30.1 (K), D31.1 (K), D32.1 (K), D33.1 (K), D34.1 (K), D35.1 (K), D36.1 (K), D37.1 (K), D38.1 (K), D39.1 (K), D40.1 (K), D41.1 (K), D42.1 (K), D43.1 (K), D44.1 (K), U1.20 (PD2)
ROW3: D45.1 (K), D46.1 (K), D47.1 (K), D48.1 (K), D49.1 (K), D50.1 (K), D51.1 (K), D52.1 (K), D53.1 (K), D54.1 (K), D55.1 (K), D56.1 (K), D57.1 (K), D58.1 (K), U1.19 (PD1)
ROW4: D59.1 (K), D60.1 (K), D61.1 (K), D62.1 (K), D63.1 (K), D64.1 (K), D65.1 (K), D66.1 (K), D67.1 (K), D68.1 (K), D69.1 (K), D70.1 (K), D71.1 (K), D72.1 (K), U1.11 (PB3)
ROW5: D73.1 (K), D74.1 (K), D75.1 (K), D76.1 (K), D77.1 (K), D78.1 (K), D79.1 (K), D80.1 (K), D81.1 (K), D82.1 (K), U1.12 (PB7)
VBUS: F1.1, J1.A4 (VBUS), J1.A9 (VBUS), J1.B4 (VBUS), J1.B9 (VBUS), U2.4 (VCC)

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
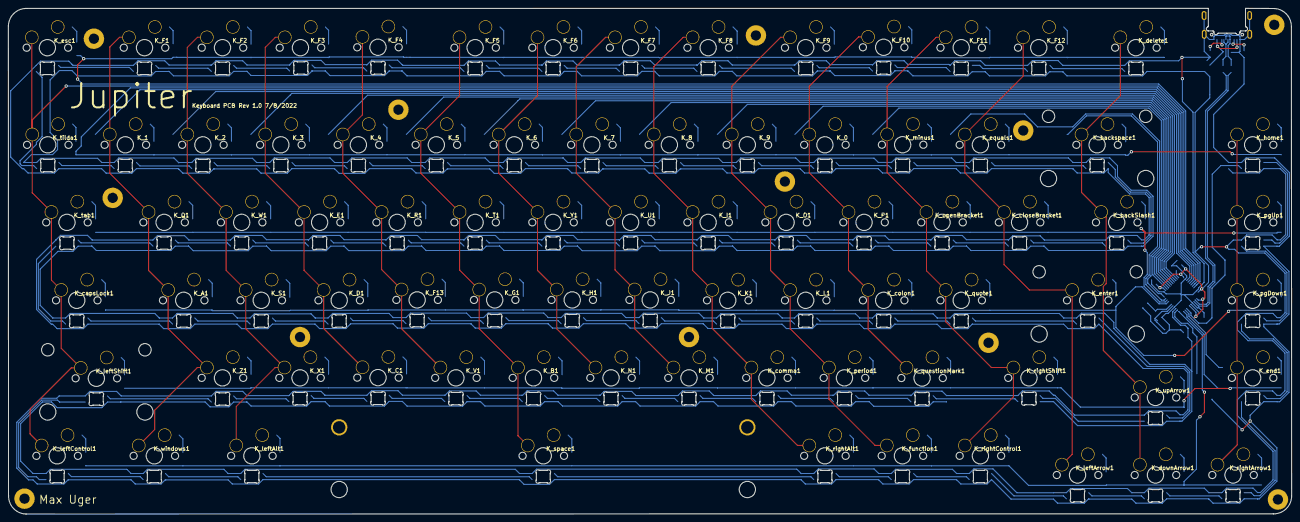
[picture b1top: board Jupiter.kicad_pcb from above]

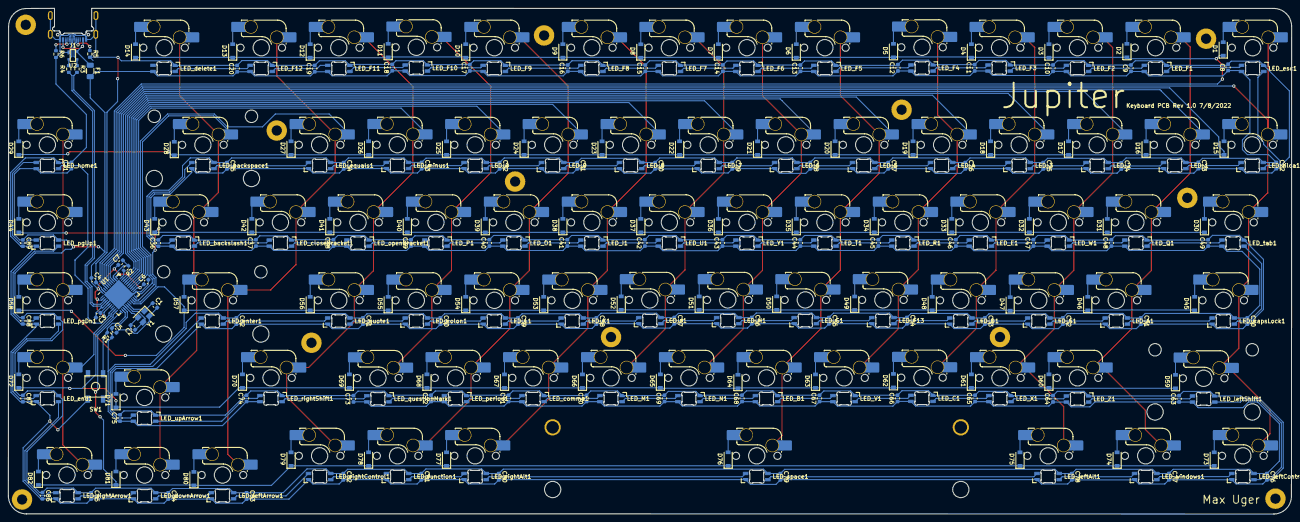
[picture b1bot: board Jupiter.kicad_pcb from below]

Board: 2 copper layers, 314.4 x 123.9 mm, 347 parts (347 on the bottom side), 199 nets.

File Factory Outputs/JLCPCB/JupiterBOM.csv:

Comment,Designator,Footprint,LCSC
"22pF","C1,C2","Capacitor_SMD:C_0603_1608Metric",""
"1uF","C3","Capacitor_SMD:C_0603_1608Metric",""
"10uF","C4","Capacitor_SMD:C_0603_1608Metric",""
"0.1uF","C5,C6,C7,C8,C9,C10,C11,C12,C13,C14,C15,C16,C17,C18,C19,C20,C21,C22,C23,C24,C25,C26,C27,C28,C29,C30,C31,C32,C33,C34,C35,C36,C37,C38,C39,C40,C41,C42,C43,C44,C45,C46,C47,C48,C49,C50,C51,C52,C53,C54,C55,C56,C57,C58,C59,C60,C61,C62,C63,C64,C65,C66,C67,C68,C69,C70,C71,C72,C73,C74,C75,C76,C77,C78,C79,C80,C81,C82,C83,C84,C85,C86,C87,C88,C89","Capacitor_SMD:C_0603_1608Metric",""
"D_Small","D1,D2,D3,D4,D5,D6,D7,D8,D9,D10,D11,D12,D13,D14,D15,D16,D17,D18,D19,D20,D21,D22,D23,D24,D25,D26,D27,D28,D29,D30,D31,D32,D33,D34,D35,D36,D37,D38,D39,D40,D41,D42,D43,D44,D45,D46,D47,D48,D49,D50,D51,D52,D53,D54,D55,D56,D57,D58,D59,D60,D61,D62,D63,D64,D65,D66,D67,D68,D69,D70,D71,D72,D73,D74,D75,D76,D77,D78,D79,D80,D81,D82","Diode_SMD:D_SOD-123",""
"500mA","F1","Fuse:Fuse_1206_3216Metric",""
"Connector_USB_C_Receptacle_USB2.0","J1","marbastlib-various:USB_C_Receptacle_HRO_TYPE-C-31-M-14",""
"MX-NoLED","K_0,K_1,K_A1,K_B1,K_backSlash1,K_backspace1,K_C1,K_capsLock1,K_closeBracket1,K_colon1,K_comma1,K_D1,K_delete1,K_downArrow1,K_E1,K_end1,K_enter1,K_equals1,K_esc1,K_F1,K_function1,K_G1,K_H1,K_home1,K_I1,K_J1,K_K1,K_L1,K_leftAlt1,K_leftArrow1,K_leftControl1,K_leftShift1,K_M1,K_minus1,K_N1,K_O1,K_openBracket1,K_P1,K_period1,K_pgDown1,K_pgUp1,K_Q1,K_questionMark1,K_quote1,K_R1,K_rightAlt1,K_rightArrow1,K_rightControl1,K_rightShift1,K_S1,K_space1,K_T1,K_tab1,K_tilda1,K_U1,K_upArrow1,K_V1,K_W1,K_windows1,K_X1,K_Y1,K_Z1,K_2,K_F2,K_3,K_F3,K_4,K_F4,K_5,K_F5,K_6,K_F6,K_7,K_F7,K_8,K_F8,K_9,K_F9,K_F10,K_F11,K_F12,K_F13","marbastlib-mx:SW_MX_HS_1u",""
"SK6812MINI-E","LED_0,LED_1,LED_A1,LED_backspace1,LED_capsLock1,LED_colon1,LED_D1,LED_downArrow1,LED_end1,LED_enter1,LED_equals1,LED_function1,LED_G1,LED_H1,LED_J1,LED_K1,LED_L1,LED_leftAlt1,LED_leftArrow1,LED_leftControl1,LED_minus1,LED_pgDn1,LED_pgUp1,LED_quote1,LED_rightAlt1,LED_rightArrow1,LED_rightControl1,LED_S1,LED_space1,LED_tilda1,LED_windows1,LED_2,LED_3,LED_4,LED_5,LED_6,LED_7,LED_8,LED_9,LED_F13","marbastlib-mx:LED_MX_6028R",""
"SK6812MINI-E","LED_B1,LED_backslash1,LED_C1,LED_closeBracket1,LED_comma1,LED_delete1,LED_E1,LED_esc1,LED_F1,LED_home1,LED_I1,LED_leftShift1,LED_M1,LED_N1,LED_O1,LED_openBracket1,LED_P1,LED_period1,LED_Q1,LED_questionMark1,LED_R1,LED_rightShift1,LED_T1,LED_tab1,LED_U1,LED_upArrow1,LED_V1,LED_W1,LED_X1,LED_Y1,LED_Z1,LED_F2,LED_F3,LED_F4,LED_F5,LED_F6,LED_F7,LED_F8,LED_F9,LED_F10,LED_F11,LED_F12","marbastlib-mx:LED_MX_6028R-FLIPPED",""
"10k","R1","Resistor_SMD:R_0603_1608Metric",""
"1k","R2","Resistor_SMD:R_0603_1608Metric",""
"22","R3,R4","Resistor_SMD:R_0603_1608Metric",""
"5.1k","R5,R6","Resistor_SMD:R_0603_1608Metric",""
"SW_Push","SW1","random-keyboard-parts:SKQG-1155865",""
"ATmega32U4-M","U1","Package_DFN_QFN:QFN-44-1EP_7x7mm_P0.5mm_EP5.2x5.2mm",""
"PRTR5V0U2X","U2","random-keyboard-parts:SOT143B",""
"16MHz","Y1","Crystal:Crystal_SMD_3225-4Pin_3.2x2.5mm",""

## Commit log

2022-07-13 Finished MCU schematic
2022-07-13 finished matrix
2022-07-14 Finished LED matrix
2022-07-14 labeled LED matrix
2022-07-14 Finished capacitor matrix
2022-07-14 Added 4 pin connector for usb-c daughter board
2022-07-14 Assigned Footprints
2022-07-14 Placed keys on board
2022-07-14 Finished LED placement
2022-07-14 Flipped LED footprint
2022-07-14 Finished diode placement
2022-07-16 Finished vertical matrix traces
2022-07-17 Finished LED capacitor placement
2022-07-17 added stabilizers
2022-07-17 Added traces
2022-07-17 traces
2022-07-17 more traces
2022-07-17 almost finished trace routing
2022-07-17 edge cuts
2022-08-07 Added usb-c submodule
2022-08-07 added another type c library
2022-08-07 Added usb connector
2022-08-07 Finished usb-c assembly
2022-08-07 Corrected LED orientation
2022-08-08 Finished trace routing
2022-08-08 silkscreen
2022-08-08 Added mounting holes
2022-08-08 Changed diode footprint
2022-08-08 generated fabrication outputs (JLCPCB)
2022-08-08 Corrected a spelling mistake on the bottom-pos.csv
2022-08-10 Added images
